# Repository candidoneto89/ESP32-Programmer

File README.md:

# ESP32-Programmer

This is a serial bridge for programming custom ESP32 boards, with auto-reset feature, so you shouldn't have to manually push buttons to enter boot mode. The board can also power simple ESP32 boards and has some standard circuit protections. 

**Features:**
- USB-C Connector
- ESD, overcurrent and reverse current protection
- CP2104 enabled USB-to-UART Bridge
- 3.3V ~ 600mA regulator
- Auto-reset circuit
- Boot and Reset buttons.
  
# Building
## PCB BOM

|Parts      |Value           |Package             |Qty|
|-----------|----------------|--------------------|---|
|C1, C2, C5 |10uF            |0603-CAP            |3  |
|C3         |1uF             |0603-CAP            |1  |
|C4         |10uF            |C0805               |1  |
|C6         |1uF             |C0805               |1  |
|D1, D2, D3 |BAT60A          |SOD-323             |3  |
|F1         |1.5A PTC FUSE   |PTC1206             |1  |
|J2         |USB-C-4105_REVA |GCT_USB4105_REVA    |1  |
|PWR        |RED LED         |0805_LED            |1  |
|Q1         |UMH3N           |SOT65P230X110-6N    |1  |
|R3, R4, R10|5.1k            |R0805               |3  |
|R5, R8, R9 |10k             |R0805               |3  |
|R6         |4.7k            |R0805               |1  |
|R7         |100k            |R0805               |1  |
|RX         |YELLOW LED      |0805_LED            |1  |
|S1, S2     |KMR621NG SWITCH |KMR621NG_LFS        |2  |
|TX         |ORANGE LED      |0805_LED            |1  |
|U1         |CP2104-F03-GM   |QFN50P400X400X80-25N|1  |
|U2         |USBLC6-2SC6     |SOT95P280X145-6N    |1  |
|U3         |AP2112M-3.3TRG1 |AP2112M-3.3TRG1_DIO |1  |
|X1         |BM07B-SRSS-TBB  |BM07B-SRSS-TB       |1  |

## Assembly partlist:

### FDM case:
- 4x M2 3mmx3mm threaded inserts
- 4x M2 5mm Hex Socket Cap Screw (or similar)

### Stacked acrylic case:
- 8x M2 3mmx3mm threaded inserts
- 8x M2 5mm Hex Socket Cap Screw (or similar)

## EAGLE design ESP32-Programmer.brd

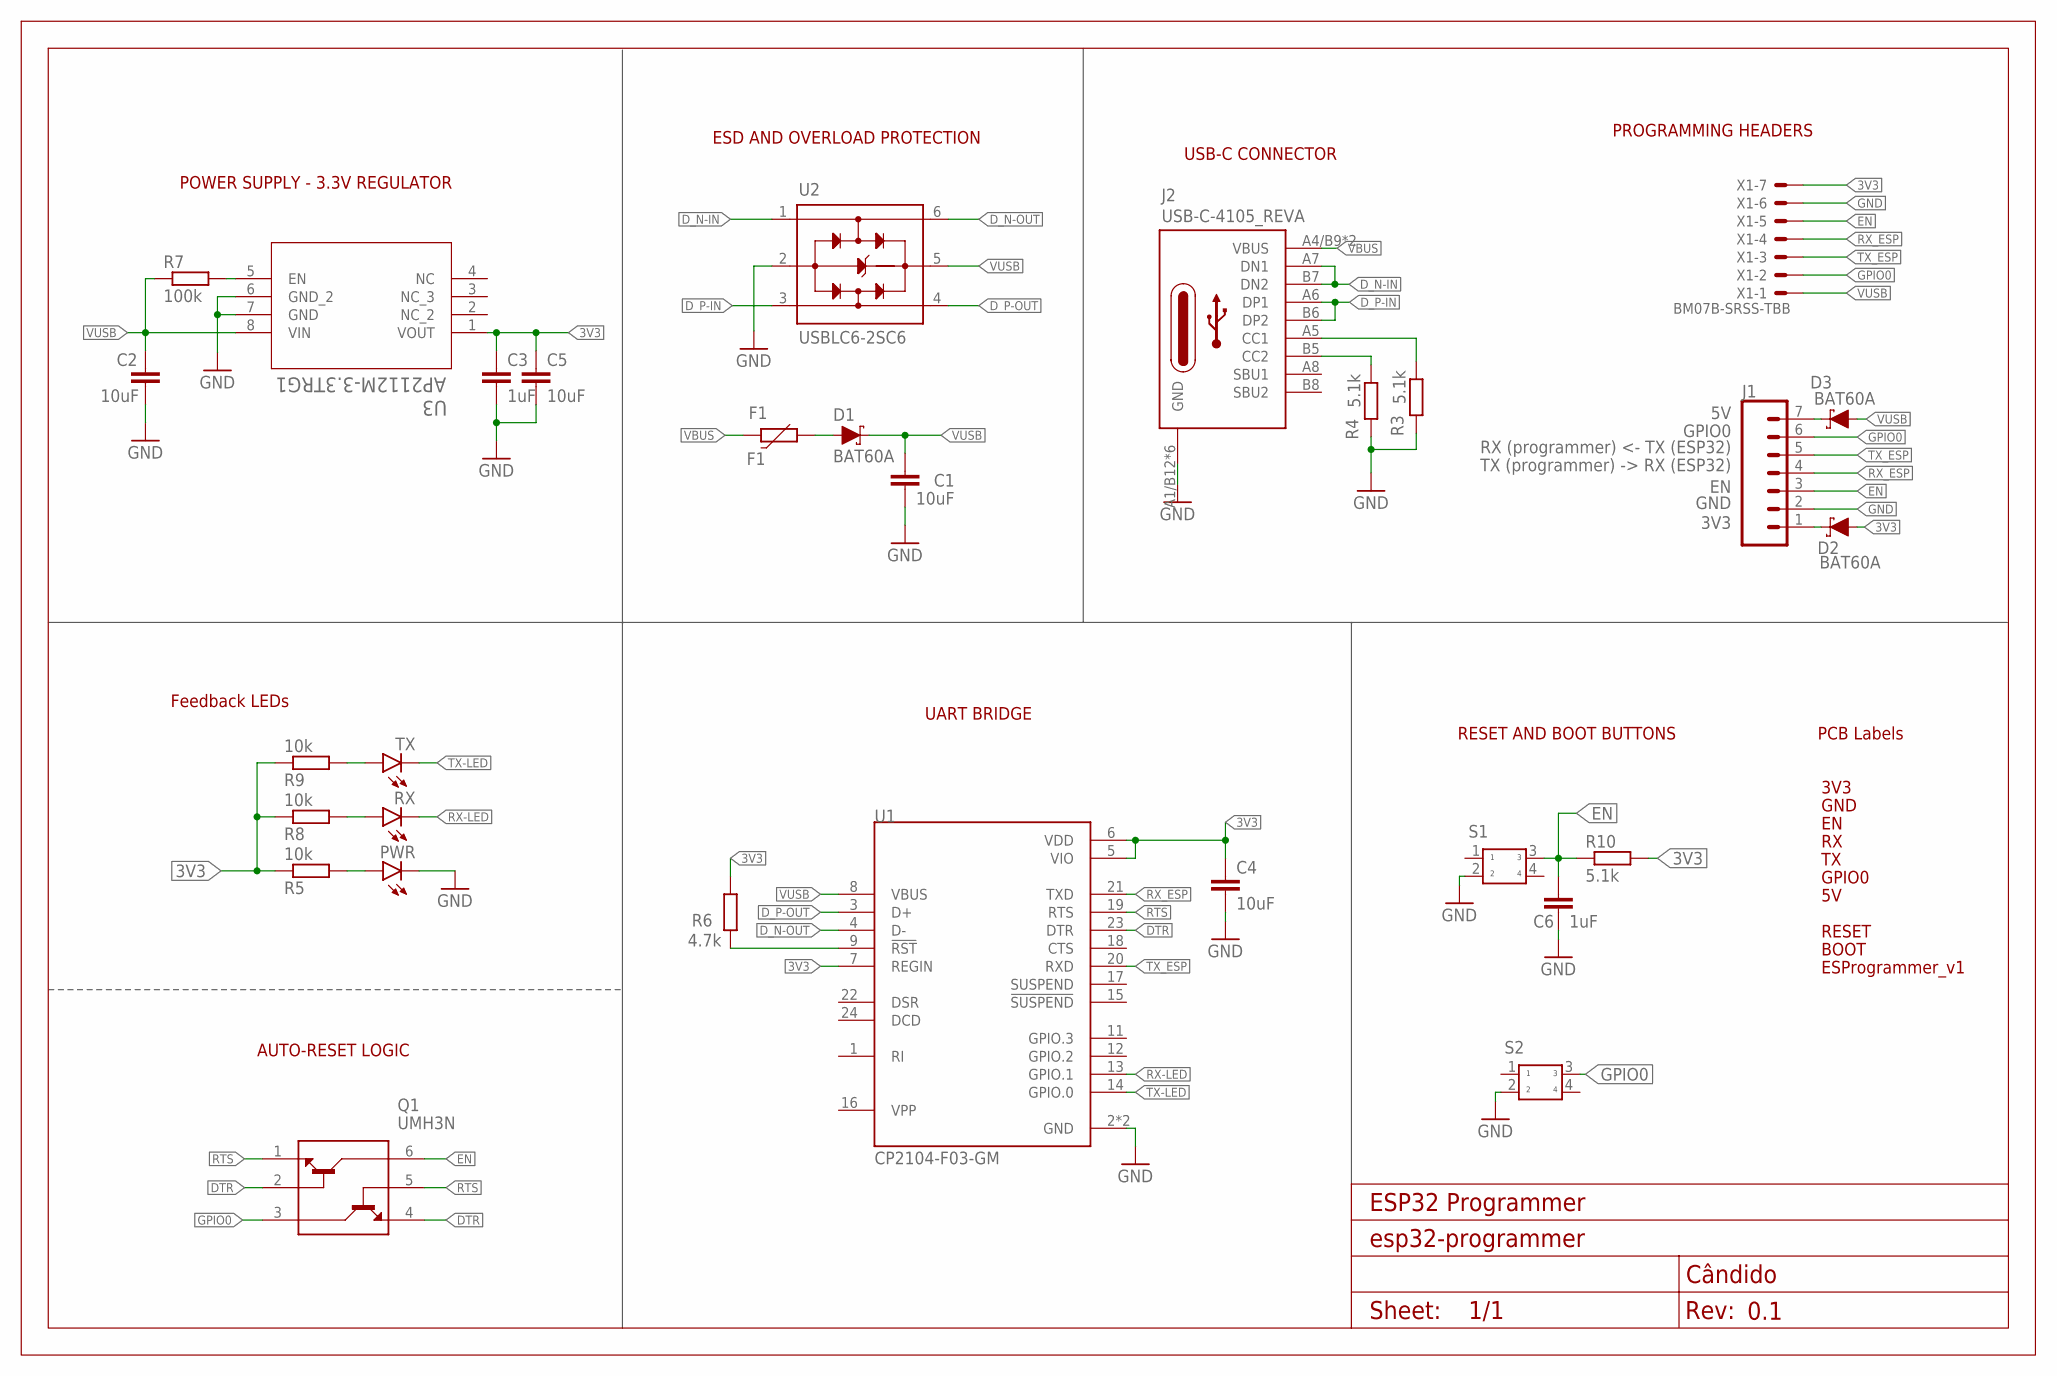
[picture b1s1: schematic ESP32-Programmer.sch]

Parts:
C1, C2, C5: 10uF; 0603-CAP
C3: 1uF; 0603-CAP
C4: 10uF; C0805
C6: 1uF; C0805
D1, D2, D3: BAT60A; SOD-323
F1: F1; PTC1206
FRAME1: FRAME_A4; FRAME-A4
J1: CONN-07NO_SILK; 1X07_NO_SILK
J2: USB-C-4105_REVA; GCT_USB4105_REVA
PWR: LEDRED-0805; LED_0805_RED
Q1: UMH3N; SOT65P230X110-6N
R3, R4, R10: 5.1k; R0805
R5, R8, R9: 10k; R0805
R6: 4.7k; R0805
R7: 100k; R0805
RX: LEDYELLOW-0805; LED_0805_YELLOW
S1, S2: KMR621NG_LFS
TX: LEDORANGE-0805; LED_0805_ORANGE
U1: CP2104-F03-GM; QFN50P400X400X80-25N
U2: USBLC6-2SC6; SOT95P280X145-6N
U3: AP2112M-3.3TRG1; AP2112M-3.3TRG1_DIO
U$1: BOOT0
U$2: GND0
U$3: 3V30
U$4: 5V0
U$5: EN0
U$6: GPIO00
U$7: RX0
U$8: TX0
U$9: RESET0
U$12: ESPROGRAMMER_V10
X1: BM07B-SRSS-TBB; BM07B-SRSS-TB

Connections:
3V3: C3.1, C4.1, C5.1, D2.A, R5.1, R6.2, R8.1, R9.1, R10.2, U1.5 (VIO), U1.6 (VDD), U1.7 (REGIN), U3.1 (VOUT), X1.7
CC1: J2.A5 (CC1), R3.1
CC2: J2.B5 (CC2), R4.1
DTR: Q1.2 (B1), Q1.4 (E2), U1.23 (DTR)
D_N-IN: J2.A7 (DN1), J2.B7 (DN2), U2.1 (I/O1_IN)
D_N-OUT: U1.4 (D-), U2.6 (I/O1_OUT)
D_P-IN: J2.A6 (DP1), J2.B6 (DP2), U2.3 (I/O2_IN)
D_P-OUT: U1.3 (D+), U2.4 (I/O2_OUT)
EN: C6.1, J1.3, Q1.6 (C1), R10.1, S1.3, X1.5
GND: C1.2, C2.2, C3.2, C4.2, C5.2, C6.2, J1.2, J2.A1/B12 (GND), J2.B1/A12 (GND), J2.G1 (GND), J2.G2 (GND), J2.G3 (GND), J2.G4 (GND), PWR.C, R3.2, R4.2, S1.2, S2.2, U1.2 (GND), U1.25 (GND), U2.2 (GND), U3.6 (GND_2), U3.7 (GND), X1.6
GPIO0: J1.6, Q1.3 (C2), S2.3, X1.2
unnamed: R6.1, U1.9 (!RST)
unnamed: D2.C, J1.1
unnamed: D3.C, J1.7
unnamed: PWR.A, R5.2
unnamed: R7.2, U3.5 (EN)
unnamed: R8.2, RX.A
unnamed: R9.2, TX.A
unnamed: D1.A, F1.2
RTS: Q1.1 (E1), Q1.5 (B2), U1.19 (RTS)
RX-LED: RX.C, U1.13 (GPIO.1)
RX_ESP: J1.4, U1.21 (TXD), X1.4
TX-LED: TX.C, U1.14 (GPIO.0)
TX_ESP: J1.5, U1.20 (RXD), X1.3
VBUS: F1.1, J2.A4/B9 (VBUS), J2.B4/A9 (VBUS)
VUSB: C1.1, C2.1, D1.C, D3.A, R7.1, U1.8 (VBUS), U2.5 (VBUS), U3.8 (VIN), X1.1

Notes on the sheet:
POWER SUPPLY - 3.3V REGULATOR
USB-C CONNECTOR
UART BRIDGE
AUTO-RESET LOGIC
RX (programmer) <- TX (ESP32)
TX (programmer) -> RX (ESP32)
3V3
GPIO0
GND
Feedback LEDs
ESD AND OVERLOAD PROTECTION
PROGRAMMING HEADERS
RESET AND BOOT BUTTONS
PCB Labels

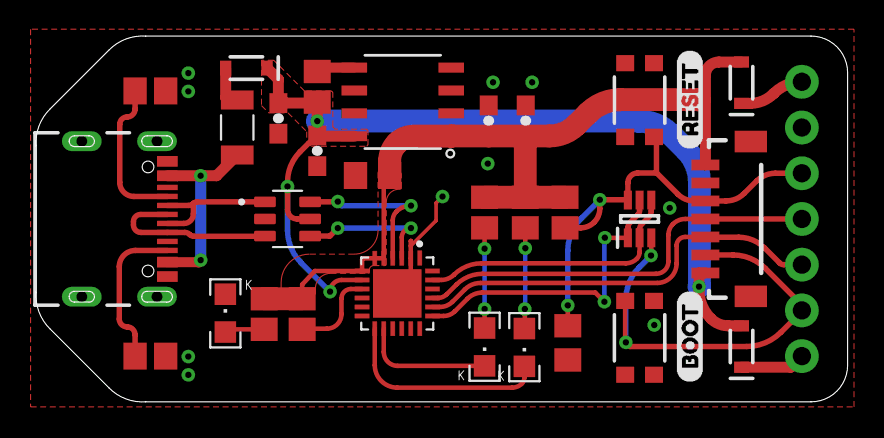
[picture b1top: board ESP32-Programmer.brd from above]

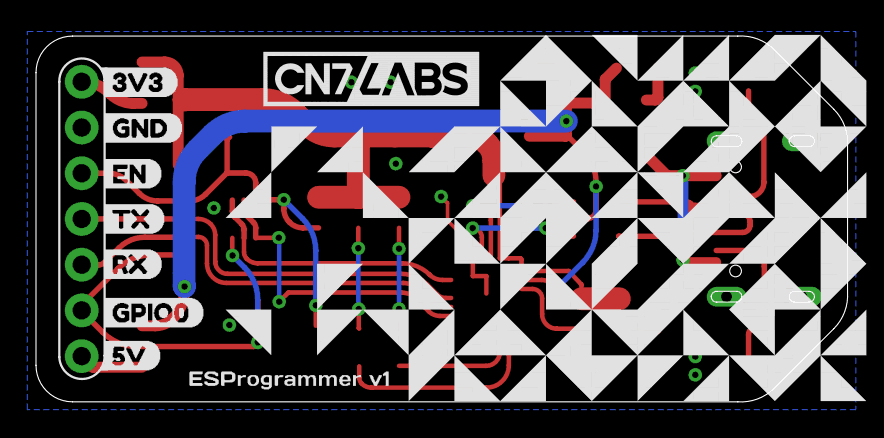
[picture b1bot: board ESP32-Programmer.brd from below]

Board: 2 copper layers, 45.1 x 20.3 mm, 43 parts (10 on the bottom side), 26 nets.

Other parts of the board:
U$10: CN7LABS-1
U$11: TRUCHET-TILE-1

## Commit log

2024-06-09 gitignore
2025-09-27 fdm case added

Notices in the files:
parts and their libraries:
SparkFun-DiscreteSemi: Licensing: Creative Commons ShareAlike 4.0 International - https://creativecommons.org/licenses/by-sa/4.0
COPYRIGHT: Copyright (C) 2022 Ultra Librarian. All rights reserved.
